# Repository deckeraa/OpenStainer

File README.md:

# slide-stainer

The OpenStainer is open-source, open-hardware automated slide stainer for laboratory use (e.g. histology, nanotech research).

Note: the OpenStainer is not yet released. This message will be removed from the README when the project has shipped it's 1.0 version.

## Development Mode

### Run application:
Boot an RT-PREEMPT-patched Linux distro on a Raspberry Pi.
The RT-PREEMPT patch is needed for smooth motor control since the stepper control signal is generated directly on the Pi.

To build the Rust web server (./src/main.rs),
you'll need to use Nightly Rust, due to some crates (namely Rocket) that require it:
```
rustup override set nightly
```

Then build and run the binary.
The binary must be run with sudoer priveleges since it sets thread priority to real-time for purposes of motion control.
```
cargo build && sudo ./target/debug/rmrm
```

Finally, start up the Clojurescript front-end

```
lein figwheel dev devcards
```

Figwheel will automatically push cljs changes to the browser.

Wait a bit, then browse to [http://localhost:3449](http://localhost:3449).

## Configuring the software to auto-start on Pi boot
In /etc/rc.local, place the following:
```
su -l pi /home/pi/code/slide-stainer/run.sh &
```

In /etc/xdg/lxsession/LXDE-pi/autostart, place the following:
```
chromium-browser http://localhost:8000/index.html --kiosk
```

## Production Build

```
lein clean
lein cljsbuild once min
```

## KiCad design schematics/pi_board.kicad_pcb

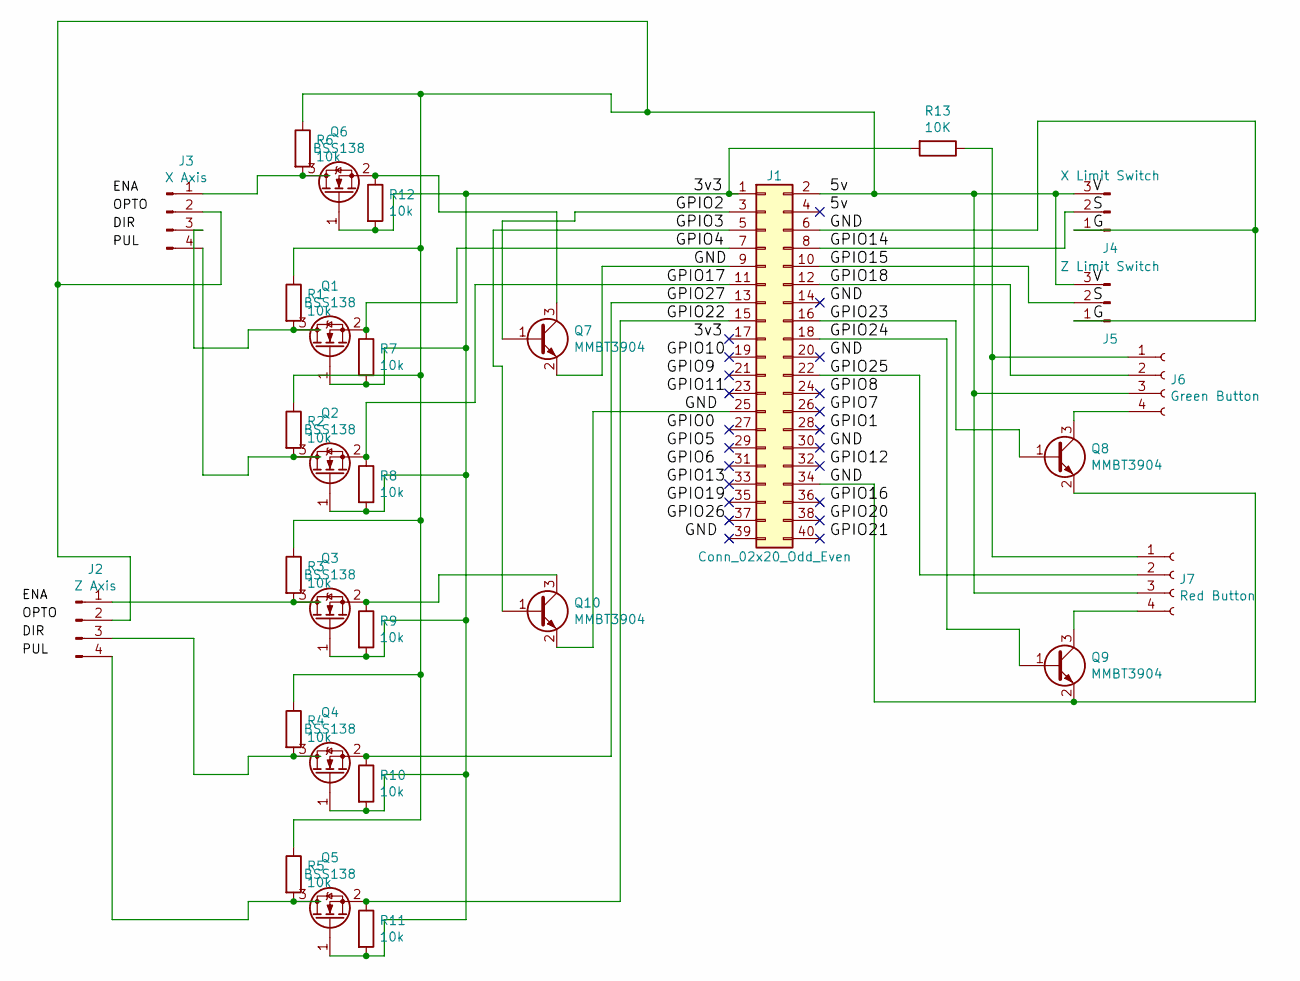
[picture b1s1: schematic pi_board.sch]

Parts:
J1: Conn_02x20_Odd_Even; PinHeader_2x20_P2.54mm_Vertical
J2: Z Axis; PinHeader_1x04_P2.54mm_Vertical
J3: X Axis; PinHeader_1x04_P2.54mm_Vertical
J4: X Limit Switch; PinHeader_1x03_P2.54mm_Vertical
J5: Z Limit Switch; PinHeader_1x03_P2.54mm_Vertical
J6: Green Button; PinHeader_1x04_P2.54mm_Vertical
J7: Red Button; PinHeader_1x04_P2.54mm_Vertical
Q1, Q2, Q3, Q4, Q5, Q6: BSS138; SOT-23
Q7, Q8, Q9, Q10: MMBT3904; SOT-23
R1, R2, R3, R4, R5, R6, R7, R8, R9, R10, R11, R12: 10k; R_1206_3216Metric_Pad1.42x1.75mm_HandSolder
R13: 10K; R_1206_3216Metric_Pad1.42x1.75mm_HandSolder

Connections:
/3v3: J1.1, Q1.1 (G), Q2.1 (G), Q3.1 (G), Q4.1 (G), Q5.1 (G), Q6.1 (G), R7.2, R8.2, R9.2, R10.2, R11.2, R12.2, R13.2
/5v: J1.2, J2.2, J3.2, J4.3, J5.3, J6.3, J7.3, R1.1, R2.1, R3.1, R4.1, R5.1, R6.1
/G: J1.6, J1.9, J1.25, J1.34, J4.1, J5.1, Q7.2 (E), Q8.2 (E), Q9.2 (E), Q10.2 (E)
/GPIO2: J1.3, Q7.1 (B)
/GPIO3: J1.5, Q10.1 (B)
/GPIO4: J1.7, Q1.2 (S), R7.1
/GPIO14: J1.8, J4.2
/GPIO15: J1.10, J5.2
/GPIO17: J1.11, Q2.2 (S), R8.1
/GPIO18: J1.12, J6.2
/GPIO22: J1.15, Q5.2 (S), R11.1
/GPIO23: J1.16, Q8.1 (B)
/GPIO24: J1.18, Q9.1 (B)
/GPIO25: J1.22, J7.2
/GPIO27: J1.13, Q4.2 (S), R10.1
unnamed: J2.1, Q3.3 (D), R3.2
unnamed: J2.3, Q4.3 (D), R4.2
unnamed: J2.4, Q5.3 (D), R5.2
unnamed: J3.1, Q6.3 (D), R6.2
unnamed: J3.3, Q1.3 (D), R1.2
unnamed: J3.4, Q2.3 (D), R2.2
unnamed: J6.1, J7.1, R13.1
unnamed: J6.4, Q8.3 (C)
unnamed: J7.4, Q9.3 (C)
unnamed: Q6.2 (S), Q7.3 (C), R12.1
unnamed: Q3.2 (S), Q10.3 (C), R9.1

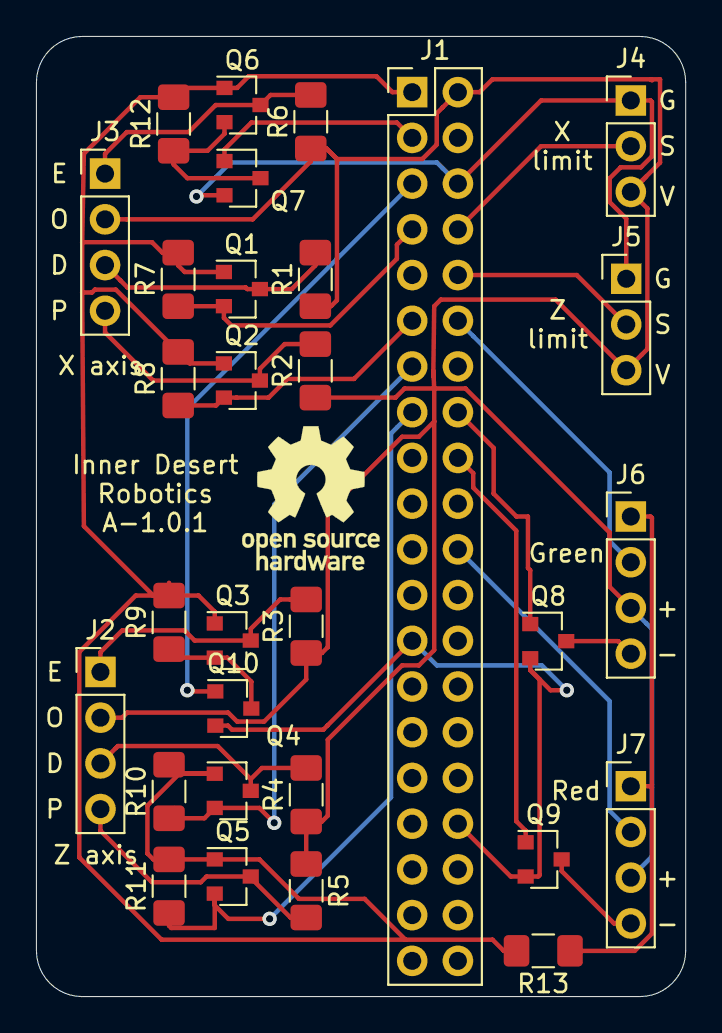
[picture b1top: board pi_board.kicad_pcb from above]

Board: 2 copper layers, 36.1 x 53.3 mm, 30 parts (0 on the bottom side), 26 nets.

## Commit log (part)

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2019-11-28 Basic LED blinking via REST.
2019-11-29 Basic html button that blinks an LED.
2019-11-30 Add pin controls and pulse controls. Get stepper spinning smoothly. Still figuring out how the DIR pin works.
2020-01-02 Rename project from test-reagent to slide-stainer.
2020-01-02 Add basic graphql support in the backend.
2020-01-03 Add support for pulling back the ip address
2020-01-03 Start to add in pin defs.
2020-01-03 Add handling for returning pin number using the pin setup index. Add support for logical_value.
2020-01-03 Add an LED on pin 13.
2020-01-09 Added a pins query
2020-01-09 Add set_pin mutation. Also add query to pull back state-atom.
2020-01-09 Add in screen selection header bar.
2020-01-13 Added pulsing, but not ramp-up functions.
2020-01-16 Add in stepperX config and rename the old stepperX to stepperZ.
2020-01-16 Write move-relative
2020-01-16 Basic absolute position API.
2020-01-18 WIP adding switch watcher.
2020-01-18 Add basic jog control.
2020-01-19 Add graphql-click-handler abstraction and a button to clean up pins, as well as the init-watcher function.
2020-01-21 Write get-input-pin-defs-for-gpio-lib
2020-01-21 Init watcher using a transformed pin defs rather than a hard-coded map.
2020-01-21 Make init-status-atm multi-variadic.
2020-01-21 Support inversion for input pins when updating the status atom.
2020-01-21 Add bounds-setting code in move-to-position for when the limit switch gets hit.
2020-01-21 WIP: start work on adding support for GraphQL variables.
2020-01-22 Clean up code for position-readout-jog-control
2020-01-22 Switch out pin 22 to pin 21.
2020-01-23 Move pulse positioning logic into move-by-pulses.
2020-01-23 Rename :position to :position-in-pulses
2020-01-26 Use a busy-wait method for signal generation and add an absolute position control.
2020-01-26 Add jar control
2020-01-27 Move pin def manipulation functions to defs.clj
2020-01-27 Add board_setup.clj
2020-01-27 Move pulses-to-inches functions over.
2020-01-27 Remove alternating-leds
2020-01-28 Fix pulse-catch-up causing missed steps.
2020-01-28 Switch to passing reagent atoms through the program creation components.
2020-01-28 Update jar number when substance is changed in a step.
2020-01-28 Create jar-selector to determine which jar to move to in the case of identical substances.
2020-01-28 Make jar selection changeable.
2020-01-29 Add plus button (non-functioning) to Procedure Steps
2020-01-29 Add in devcards.
2020-01-29 Add abliity to add and remove steps.
2020-01-29 Make the number of jars configurable.
2020-01-30 Add on-mouse-down handler to call (.preventDefault e) as well as some CSS changes to the on-screen keyboard.
2020-01-30 Forgot to save slide-stainer.css before committing.
2020-01-30 Implement proper backspace support.
2020-01-30 Add devcards-specific styles.
2020-01-30 Make onscreen-keyboard fixed-positioning and support show/hide.
2020-01-30 CSS improvements to onscreen-keyboard.
2020-01-30 Remove stray :on-focus handler that was clobbering osk-atm.
2020-01-30 Factor out done button.
2020-01-30 Implement shifting.
2020-01-30 Add support for on-blur and for passing in :size so that the time inputs can use osk-input.
2020-01-31 Support more shifted buttons.
2020-02-05 hook up stepper-Z-limit-switch-high
2020-02-05 Add limit switch to X axis.
2020-02-06 Implement homing
2020-02-07 Update pin defs and add latency warning.
2020-02-08 Spend less time waiting before spinning up motors
2020-02-08 Print message when limit switch unexpectedly hit.
2020-02-09 Add alarms-control-card
2020-02-09 Auto-load alarms
2020-02-09 Add alarms status piggyback onto the jars control.
2020-02-10 Fix a lock leak in move-by-pulses.
2020-02-10 Add alarm support to axis graphql resolver to make alarms populate correctly upon jar movement.
2020-02-10 Add ability to repeat a procedure a set number of times; also introduce motion-test-program to repeatedly test motion from jar to jar.
2020-02-10 Add graphql schema representation of the procedure.
2020-02-10 Add a mutation for save_procedure.
2020-02-11 Add convert-keywords-to-strings
2020-02-11 Implement round-trip to CouchDB and back for saving a procedure on the sample-program screen.
2020-02-11 Add styles and event handlers to procedure-selection.
2020-02-11 Add in procedure load from database.
2020-02-11 Make procedure-selection load the selection list from the database.
2020-02-11 Add graphql/empty-procedure to fix issue #3: Create single place to define logic for new procedures
2020-02-11 Make pressing enter close the on-screen keyboard; make clicking the field again re-open it.
2020-02-11 Add a run button and switch run-program-by-name to run-program-by-id
2020-02-11 Implement different max speeds for each axis.
2020-02-12 Fix issue with jar_number being parsed and with keywords being misnamed
2020-02-12 Add current_procedure_id and current_procedure_name
2020-02-12 Add procedure-run.cljs
2020-02-12 back off a quarter inch in the up position so we're not constantly triggering the limit switch
2020-02-12 Add procedure repeat functionality.
2020-02-13 WIP: Switch run button to open up the run screen.
2020-02-13 Move current procedure status information to its own cursor.
2020-02-13 Take machine out of stopped status when a run-program is called.
2020-02-14 Add a button for dropping the motor lock.
2020-02-14 Rename pulse-lock to motor-lock.
2020-02-14 Add additional checks for the stopped flag in the multi-part moves (such as move-to-jar).
2020-02-14 Fix issue where position would be set incorreclty when the e-stop was used during a move.
2020-02-14 Start the program thread as the highest priority of the thread group.
2020-02-14 Remove old, unneeded REST routes.
2020-02-15 Update procedure-run's refresh button to use the factored-out refresh-fn.
2020-02-15 WIP: some progress on updating the remaining time.
2020-02-16 Add a bell icon to the header.
2020-02-16 Finishing switch over to :screen-stack for screen state management.
2020-02-16 Center the settings header in the settings page.
2020-02-17 Add positions-and-home control
2020-02-17 Make the settings home button perform the homing operation.
2020-02-17 Split out atoms.cljs. Also fix some reagent issues in settings.cljs
2020-02-17 Update the position readout.
2020-02-17 Add better support for anim-fn in periodic-updater. Nothing using it yet.
2020-02-18 Have the alarms icon take the user to the settings page when clicked.
2020-02-18 Have the homing function clear pertinent alarms.
2020-02-18 Style the procedure-selection header to be like the settings screen header.
2020-02-18 Style the 'New Procedure' button.
2020-02-18 Sort procedure names alphabetically.
2020-02-18 Move always-fn to 5 second interval.
2020-02-18 Make resolve-procedures support querying all supplied fields. Fixes issue #4.
2020-02-18 Add styling to procedure styling cards.
2020-02-21 Comment out init-pins and make the home button hit up the real-time Rust micro-service.
2020-02-22 Have position_inches retrieve the position from the Real-Time Rust micro-service.
2020-02-22 Use the new run-button fn in program-creation.
2020-02-25 Produce run.sh to run everything in release mode. Also fixed a couple of issues (like underscores in file names) to enable release mode compiles.
2020-03-03 Implement workaround for #7.
2020-03-03 Add a backspace icon to the backspace button to save screen space.
2020-03-03 Add button:active style to give visual inidcation of button click.
2020-03-03 Change background color of onscreen-keyboard to be more pleasant.
2020-03-03 Move GraphQL control to settings screen, behind developer flag.
2020-03-03 text changes to procedure selection screen.
2020-03-03 Hide the jog page.
2020-03-03 Comment out the button bar at the top and add in a back button to the procedure run screen.
2020-03-04 Code cleanup.
2020-03-05 Code cleanup
2020-03-06 Add graphQL handler for axis to the Rust web server
2020-03-06 Update pi defs to the A1.0.1 board.
2020-03-07 WIP add structs for Procedure and ProcedureStep.
2020-03-07 Make repeat Option<i32> and avoid serializing when null.
2020-03-07 Finish procedures handler.
2020-03-08 WIP add save_procedure mutation. Haven't tested it yet.
2020-03-09 Add CORS support.
2020-03-09 Fix issue with parsing Juniper's GraphQL response.
2020-03-10 Get save_procedure working.
2020-03-10 Add structs for current run status as well as a skeleton run_procedure handler.
2020-03-10 Implement run_procedure.
2020-03-10 WIP. Fix typo to open up procedure_run screen after hitting the run button. Also update key names in procedure_run.cljs for the new Rust web server GraphQL API.
2020-03-11 WIP add some very rudimentary pause support.
2020-03-11 Add pausing handling when the movement to the jar is in progress.
2020-03-11 Added State<ProcedureExecutionState> to the remaining motion handlers.
2020-03-12 WIP: Add in a GraphQL attribute for run_status, but it doesn't return the actual run status yet.
2020-03-12 Make auto-start work.
2020-03-12 Fix styling on home butotn.
2020-03-13 Style the repeat field and initialize it to 1 on procedure creation.
2020-03-19 More styling changes on procedure creation screen.
2020-03-19 Add developer-mode-control.
2020-03-19 Put program atom behind the developer flag on the procedure creation screen.
2020-03-19 Improve styling of procedure steps
2020-03-20 Rename program_creation to procedure_edit.
2020-03-20 Fix the deleteProcedure graphQL mutation (needed to pass _rev in the query string to couchDB in the DELETE call) and update the procedure-edit screen to use it. This fixes the issue where the main sc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
2020-03-21 Add a toast message for saving the procedure.
2020-03-21 Improve keyboard input for minutes and seconds input.
2020-03-21 Fix bug where keyboard input via onscreen keyboard clicks wasn't working.
2020-03-24 Update README to reflect project status.
2020-03-24 Add frame CAD files.
2020-03-25 Use xset in run.sh to avoid the screen turning off mid-run.
2020-03-26 Implement button-based paused and resume for most actions during a procedure run.
2020-03-26 Add seconds countdown to the procedure run screen.
2020-03-26 Prevent refresh-handler-fn from clobbering the :seconds-remaining element of the procedure run status cursor.
2020-03-26 Add ability to move up/down during a pause while waiting.
2020-03-26 Style the procedure run screen.
2020-03-26 Add --app flag to chrumium-browser to suppress chrome popups.
2020-03-27 Support pausing during homing.
2020-03-27 Move over Pi, Stepper, and Procedure* structs.
2020-03-27 Continue pulling things out into graphql.rs and also create motion.rs.
2020-03-27 Move more functions to motion.rs
2020-03-27 Add run-query-fn to only query seconds_remaining when a procedure is running.
2020-03-27 Support pausing while moving back to the up position.
2020-03-27 Fix debug output on number of steps moved.
2020-03-27 Increment run count after each completed run.
2020-03-27 Move procedures into couchdb.rs.
2020-03-27 Create get_doc.
2020-03-28 Save settings down to CouchDB upon exiting the settings screen.
2020-03-28 Add 'stop procedure' button
2020-03-28 Add install_views to couchdb.rs
2020-03-28 Make the back gutton look like a button.
2020-03-28 Style changes to procedure run screen.
2020-03-28 Add round back button to settings page.
2020-03-28 Remove old clojure web server code.
2020-03-30 Add in motor test functions.
2020-03-30 update pulses_per_revolution to 4000 to match driver settings.
2020-03-30 Eliminate old pulse-generation functions.
2020-03-30 Add more documentation to motion.rs
2020-03-30 Clean up code in structs_and_consts.rs
2020-03-30 Eliminate old code related to alarms. Alarms were eliminated by eliminated the conditions that lead to the need for alarms.
2020-03-30 Document periodic_updater.cljs
2020-03-31 Hide the motor test and note playing controls from the settings screen.
2020-03-31 Document core.cljs
2020-03-31 Document graphql.cljs
